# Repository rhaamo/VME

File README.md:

# Dashie's VME things

## Notes
Everything might be WIP, not functionnal, broken, or eat your cat.

Some designs might uses my own KiCAD libraries: https://dev.sigpipe.me/DashieElectronics/KiCad_libraries

Gerbers in `gerbers/` dirs or `gerbers.zip` WILL probably not be up to date, generate your own after checking schematics and PCBs.

## Contact
- dashie AT otter DOT sh

## Eurocard_3U_VME
A 3U Eurocard with VME connector Px on one end, and a lot of plated holes in a 2.54mm grid, with unconnected strips (uses them as whatever you want).

## Eurocard_6U_233x160_VME
A 6U Eurocard with VME connector P1 and P2 on one end, and a very lot of plated holes in a 2.54mm grid, with ground and 5V strips.

## MVMEPI
WIP of a PCB for a raspberrypi used as a remote access control for a VME chassis.

Various input/output for signals breakout of a MVME-167, fans, temp sensors, etc.

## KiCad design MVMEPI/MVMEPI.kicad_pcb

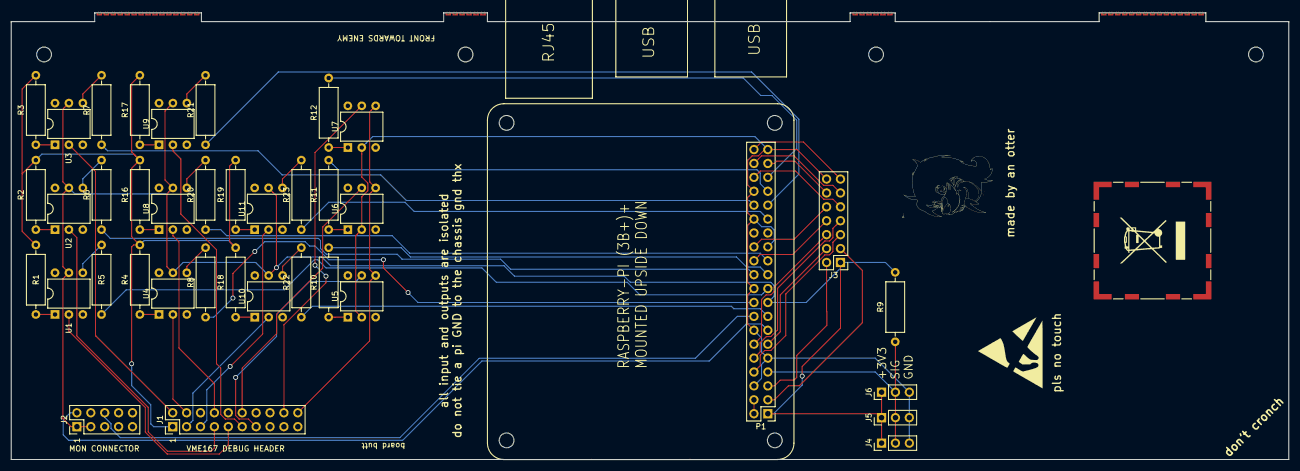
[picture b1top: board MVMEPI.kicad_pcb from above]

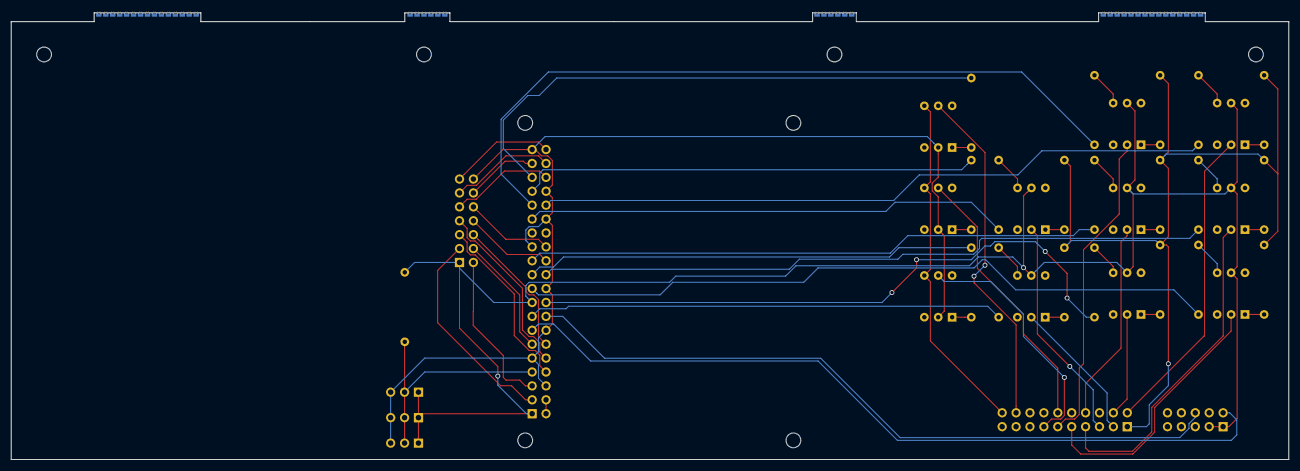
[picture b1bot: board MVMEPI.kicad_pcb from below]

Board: 2 copper layers, 233.4 x 81.6 mm, 46 parts (4 on the bottom side), 61 nets.

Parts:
J1: VME167 DEBUG HEADER; PinHeader_2x10_P2.54mm_Vertical
J2: MON CONNECTOR; PinHeader_2x05_P2.54mm_Vertical
J3: ACC; PinHeader_2x07_P2.54mm_Vertical
J4: TEMP1; PinHeader_1x03_P2.54mm_Vertical
J5: TEMP2; PinHeader_1x03_P2.54mm_Vertical
J6: TEMP3; PinHeader_1x03_P2.54mm_Vertical
MK1, MK2, MK3, MK4, MK5, MK6, MK7, MK8: M2.5; MountingHole_2.7mm_M2.5
P1: Conn_02x20_Odd_Even; PinHeader_2x20_P2.54mm_Vertical
R1, R2, R3, R4, R9, R16, R17, R18, R19: 4.7k; R_Axial_DIN0309_L9.0mm_D3.2mm_P12.70mm_Horizontal
R5, R6, R7, R8, R20, R21, R22, R23: 1k; R_Axial_DIN0309_L9.0mm_D3.2mm_P12.70mm_Horizontal
R10, R11, R12: 220; R_Axial_DIN0309_L9.0mm_D3.2mm_P12.70mm_Horizontal
U1, U2, U3, U4, U5, U6, U7, U8, U9, U10, U11: 4N25; DIP-6_W7.62mm

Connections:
+3V3: J2.1, J2.3, J3.1, J4.1, J5.1, J6.1, P1.1, P1.17, R9.2, U1.5, U2.5, U3.5, U4.5, U8.5, U9.5, U10.5, U11.5
+5V: P1.2, P1.4
/GPIO2(SDA1): J3.3, P1.3
/GPIO3(SCL1): J3.2, P1.5
/GPIO4(GCLK): J4.2, J5.2, J6.2, P1.7, R9.1
/GPIO5: P1.29, R23.1
/GPIO6: P1.31, R21.1
/GPIO7(SPI1_CE_N): J3.10, P1.26
/GPIO8(SPI0_CE_N): J3.8, P1.24
/GPIO9(SPI0_MISO): P1.21, R10.2
/GPIO10(SPI0_MOSI): P1.19, R5.1
/GPIO11(SPI0_SCK): P1.23, R20.1
/GPIO12(PWM0): P1.32, R7.1
/GPIO13(PWM1): P1.33, R11.2
/GPIO14(TXD0): J3.5, P1.8
/GPIO15(RXD0): J3.7, P1.10
/GPIO16: J3.9, P1.36
/GPIO17(GEN0): J3.4, P1.11
/GPIO18(GEN1)(PWM0): J3.6, P1.12
/GPIO19(SPI1_MISO): P1.35, R12.2
/GPIO20(SPI1_MOSI): J3.11, P1.38
/GPIO21(SPI1_SCK): J3.13, P1.40
/GPIO22(GEN3): P1.15, R22.1
/GPIO23(GEN4): J2.6, P1.16
/GPIO24(GEN5): P1.18, R8.1
/GPIO25(GEN6): P1.22, R6.1
/GPIO26: J3.12, P1.37
/GPIO27(GEN2): J2.2, P1.13
GND: J3.14, J4.3, J5.3, J6.3, P1.6, P1.9, P1.14, P1.20, P1.25, P1.30, P1.34, P1.39, U5.2, U6.2, U7.2
unnamed: R1.1, U1.1
unnamed: R2.1, U2.1
unnamed: R3.1, U3.1
unnamed: R4.1, U4.1
unnamed: R5.2, U1.4
unnamed: R6.2, U2.4
unnamed: R7.2, U3.4
unnamed: R8.2, U4.4
unnamed: R10.1, U5.1
unnamed: R11.1, U6.1
unnamed: R12.1, U7.1
unnamed: R16.1, U8.1
unnamed: R17.1, U9.1
unnamed: R18.1, U10.1
unnamed: R19.1, U11.1
unnamed: R20.2, U8.4
unnamed: R21.2, U9.4
unnamed: R22.2, U10.4
unnamed: R23.2, U11.4
VME_+5VRMT: J1.1, R1.2, R2.2, R3.2, R4.2, R16.2, R17.2, R18.2, R19.2
VME_ABORTSW*: J1.12, U6.5
VME_FAILLED*: J1.9, U1.2
VME_FUSELED*: J1.3, U10.2
VME_GND: J1.20, U5.4, U6.4, U7.4
VME_IRQ: J1.18, U7.5
VME_LANLED*: J1.2, U3.2
VME_RESETSW*: J1.13, U5.5
VME_RUNLED*: J1.7, U2.2
VME_SCONLED*: J1.11, U9.2
VME_SCSILED*: J1.4, U4.2
VME_STATLED*: J1.8, U8.2
VME_VMELED*: J1.5, U11.2

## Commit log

2019-11-29 Add README and MVMEPI
2019-11-29 blah
2019-11-29 Add 6U EuroCard
2019-11-29 Copy 6U to 3U
2019-11-29 Eurocard 6U: Add A-B-C and 1-5-10.. labels on silkscreen on both connectors
2019-11-29 Regen zip
2019-11-29 Update 3U from 6U
2019-11-29 Cut the card and change some dimmensions to adapt to single height VME boards
2019-11-29 good job
2019-11-29 3U EuroCard VME connector is now breaked out in an identical three rows pattern for easier prototyping
2019-11-29 Added grids
2019-11-29 Move board, replot
2019-11-30 Grid and mirror the connector on 6U
2019-11-30 images
2019-11-30 typo
2019-12-06 Fix track of GND overlapping on +5V
